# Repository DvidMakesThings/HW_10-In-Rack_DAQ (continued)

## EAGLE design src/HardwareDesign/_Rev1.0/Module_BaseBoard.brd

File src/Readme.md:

# %PROJECT_NAME% Project Design files
This repository contains source files for software and hardware designs related to the %PROJECT_NAME% project.
## Contents
- **Software**: Source code for the software components.
- **Hardware**: Design files for the hardware components.
## Usage
1. Clone the repository.
2. Navigate to the `src` directory.
3. Follow the instructions in the respective subdirectories for software and hardware.
## License
This project is licensed under the MIT License.
## Contact
For any questions or feedback, please contact:
- Email: [s.dvid@hotmail.com](mailto:s.dvid@hotmail.com)
- GitHub: [DvidMakesThings](https://github.com/DvidMakesThings)

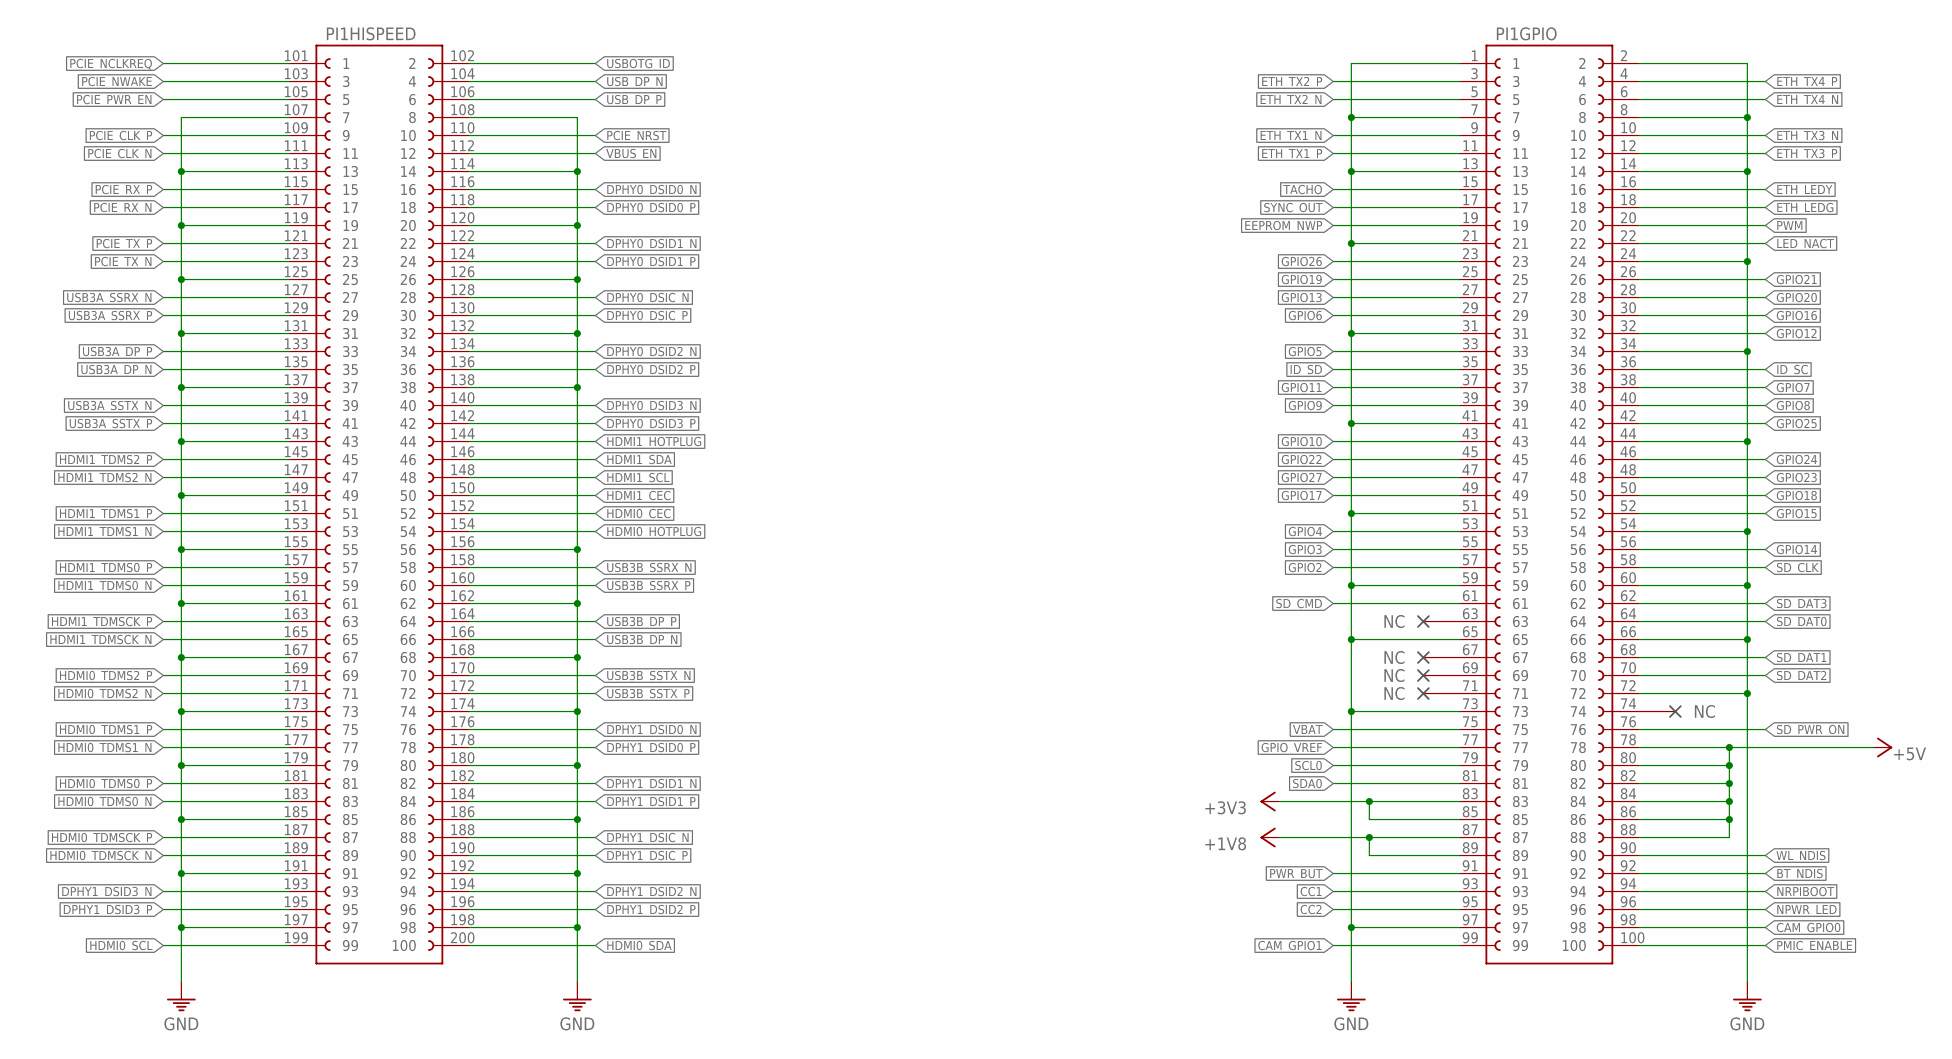
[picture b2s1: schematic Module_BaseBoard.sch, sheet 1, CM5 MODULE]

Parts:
PI1: RASPBERRY_CM5; CM5

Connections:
+1V8: PI1.87, PI1.89; also elsewhere on the board
+3V3: PI1.83, PI1.85; also elsewhere on the board
+5V: PI1.78, PI1.80, PI1.82, PI1.84, PI1.86, PI1.88; also elsewhere on the board
BT_NDIS: PI1.92; also elsewhere on the board
CAM_GPIO0: PI1.98; also elsewhere on the board
CAM_GPIO1: PI1.99; also elsewhere on the board
CC1: PI1.93; also elsewhere on the board
CC2: PI1.95; also elsewhere on the board
DPHY0_DSIC_N: PI1.128 (28); also elsewhere on the board
DPHY0_DSIC_P: PI1.130 (30); also elsewhere on the board
DPHY0_DSID0_N: PI1.116 (16); also elsewhere on the board
DPHY0_DSID0_P: PI1.118 (18); also elsewhere on the board
DPHY0_DSID1_N: PI1.122 (22); also elsewhere on the board
DPHY0_DSID1_P: PI1.124 (24); also elsewhere on the board
DPHY0_DSID2_N: PI1.134 (34); also elsewhere on the board
DPHY0_DSID2_P: PI1.136 (36); also elsewhere on the board
DPHY0_DSID3_N: PI1.140 (40); also elsewhere on the board
DPHY0_DSID3_P: PI1.142 (42); also elsewhere on the board
DPHY1_DSIC_N: PI1.188 (88); also elsewhere on the board
DPHY1_DSIC_P: PI1.190 (90); also elsewhere on the board
DPHY1_DSID0_N: PI1.176 (76); also elsewhere on the board
DPHY1_DSID0_P: PI1.178 (78); also elsewhere on the board
DPHY1_DSID1_N: PI1.182 (82); also elsewhere on the board
DPHY1_DSID1_P: PI1.184 (84); also elsewhere on the board
DPHY1_DSID2_N: PI1.194 (94); also elsewhere on the board
DPHY1_DSID2_P: PI1.196 (96); also elsewhere on the board
DPHY1_DSID3_N: PI1.193 (93); also elsewhere on the board
DPHY1_DSID3_P: PI1.195 (95); also elsewhere on the board
EEPROM_NWP: PI1.19; also elsewhere on the board
ETH_LEDG: PI1.18; also elsewhere on the board
ETH_LEDY: PI1.16; also elsewhere on the board
ETH_TX1_N: PI1.9; also elsewhere on the board
ETH_TX1_P: PI1.11; also elsewhere on the board
ETH_TX2_N: PI1.5; also elsewhere on the board
ETH_TX2_P: PI1.3; also elsewhere on the board
ETH_TX3_N: PI1.10; also elsewhere on the board
ETH_TX3_P: PI1.12; also elsewhere on the board
ETH_TX4_N: PI1.6; also elsewhere on the board
ETH_TX4_P: PI1.4; also elsewhere on the board
GND: PI1.1, PI1.2, PI1.7, PI1.8, PI1.13, PI1.14, PI1.21, PI1.24, PI1.31, PI1.34, PI1.41, PI1.44, PI1.51, PI1.54, PI1.59, PI1.60, PI1.65, PI1.66, PI1.72, PI1.73, PI1.97, PI1.107 (7), PI1.108 (8), PI1.113 (13), PI1.114 (14), PI1.119 (19), PI1.120 (20), PI1.125 (25), PI1.126 (26), PI1.131 (31), PI1.132 (32), PI1.137 (37), PI1.138 (38), PI1.143 (43), PI1.149 (49), PI1.155 (55), PI1.156 (56), PI1.161 (61), PI1.162 (62), PI1.167 (67), PI1.168 (68), PI1.173 (73), PI1.174 (74), PI1.179 (79), PI1.180 (80), PI1.185 (85), PI1.186 (86), PI1.191 (91), PI1.192 (92), PI1.197 (97), PI1.198 (98); also elsewhere on the board
GPIO2: PI1.57; also elsewhere on the board
GPIO3: PI1.55; also elsewhere on the board
GPIO4: PI1.53; also elsewhere on the board
GPIO5: PI1.33; also elsewhere on the board
GPIO6: PI1.29; also elsewhere on the board
GPIO7: PI1.38; also elsewhere on the board
GPIO8: PI1.40; also elsewhere on the board
GPIO9: PI1.39; also elsewhere on the board
GPIO10: PI1.43; also elsewhere on the board
GPIO11: PI1.37; also elsewhere on the board
GPIO12: PI1.32; also elsewhere on the board
GPIO13: PI1.27; also elsewhere on the board
GPIO14: PI1.56; also elsewhere on the board
GPIO15: PI1.52; also elsewhere on the board
GPIO16: PI1.30; also elsewhere on the board
GPIO17: PI1.49; also elsewhere on the board
GPIO18: PI1.50; also elsewhere on the board
GPIO19: PI1.25; also elsewhere on the board
GPIO20: PI1.28; also elsewhere on the board
GPIO21: PI1.26; also elsewhere on the board
GPIO22: PI1.45; also elsewhere on the board
GPIO23: PI1.48; also elsewhere on the board
GPIO24: PI1.46; also elsewhere on the board
GPIO25: PI1.42; also elsewhere on the board
GPIO26: PI1.23; also elsewhere on the board
GPIO27: PI1.47; also elsewhere on the board
GPIO_VREF: PI1.77; also elsewhere on the board
HDMI0_CEC: PI1.152 (52); also elsewhere on the board
HDMI0_HOTPLUG: PI1.154 (54); also elsewhere on the board
HDMI0_SCL: PI1.199 (99); also elsewhere on the board
HDMI0_SDA: PI1.200 (100); also elsewhere on the board
HDMI0_TDMS0_N: PI1.183 (83); also elsewhere on the board
HDMI0_TDMS0_P: PI1.181 (81); also elsewhere on the board
HDMI0_TDMS1_N: PI1.177 (77); also elsewhere on the board
HDMI0_TDMS1_P: PI1.175 (75); also elsewhere on the board
HDMI0_TDMS2_N: PI1.171 (71); also elsewhere on the board
HDMI0_TDMS2_P: PI1.169 (69); also elsewhere on the board
HDMI0_TDMSCK_N: PI1.189 (89); also elsewhere on the board
HDMI0_TDMSCK_P: PI1.187 (87); also elsewhere on the board
HDMI1_CEC: PI1.150 (50); also elsewhere on the board
HDMI1_HOTPLUG: PI1.144 (44); also elsewhere on the board
HDMI1_SCL: PI1.148 (48); also elsewhere on the board
HDMI1_SDA: PI1.146 (46); also elsewhere on the board
HDMI1_TDMS0_N: PI1.159 (59); also elsewhere on the board
HDMI1_TDMS0_P: PI1.157 (57); also elsewhere on the board
HDMI1_TDMS1_N: PI1.153 (53); also elsewhere on the board
HDMI1_TDMS1_P: PI1.151 (51); also elsewhere on the board
HDMI1_TDMS2_N: PI1.147 (47); also elsewhere on the board
HDMI1_TDMS2_P: PI1.145 (45); also elsewhere on the board
HDMI1_TDMSCK_N: PI1.165 (65); also elsewhere on the board
HDMI1_TDMSCK_P: PI1.163 (63); also elsewhere on the board
ID_SC: PI1.36; also elsewhere on the board
ID_SD: PI1.35; also elsewhere on the board
LED_NACT: PI1.22
NPWR_LED: PI1.96; also elsewhere on the board
NRPIBOOT: PI1.94; also elsewhere on the board
PCIE_CLK_N: PI1.111 (11); also elsewhere on the board
PCIE_CLK_P: PI1.109 (9); also elsewhere on the board
PCIE_NCLKREQ: PI1.101 (1); also elsewhere on the board
PCIE_NRST: PI1.110 (10); also elsewhere on the board
PCIE_NWAKE: PI1.103 (3); also elsewhere on the board
PCIE_PWR_EN: PI1.105 (5); also elsewhere on the board
PCIE_RX_N: PI1.117 (17); also elsewhere on the board
PCIE_RX_P: PI1.115 (15); also elsewhere on the board
PCIE_TX_N: PI1.123 (23); also elsewhere on the board
PCIE_TX_P: PI1.121 (21); also elsewhere on the board
PMIC_ENABLE: PI1.100; also elsewhere on the board
PWM: PI1.20; also elsewhere on the board
PWR_BUT: PI1.91; also elsewhere on the board
SCL0: PI1.79; also elsewhere on the board
SDA0: PI1.81; also elsewhere on the board
SD_CLK: PI1.58; also elsewhere on the board
SD_CMD: PI1.61; also elsewhere on the board
SD_DAT0: PI1.64; also elsewhere on the board
SD_DAT1: PI1.68; also elsewhere on the board
SD_DAT2: PI1.70; also elsewhere on the board
SD_DAT3: PI1.62; also elsewhere on the board
SD_PWR_ON: PI1.76; also elsewhere on the board
SYNC_OUT: PI1.17; also elsewhere on the board
TACHO: PI1.15; also elsewhere on the board
USB3A_DP_N: PI1.135 (35); also elsewhere on the board
USB3A_DP_P: PI1.133 (33); also elsewhere on the board
USB3A_SSRX_N: PI1.127 (27); also elsewhere on the board
USB3A_SSRX_P: PI1.129 (29); also elsewhere on the board
USB3A_SSTX_N: PI1.139 (39); also elsewhere on the board
USB3A_SSTX_P: PI1.141 (41); also elsewhere on the board
USB3B_DP_N: PI1.166 (66); also elsewhere on the board
USB3B_DP_P: PI1.164 (64); also elsewhere on the board
USB3B_SSRX_N: PI1.158 (58); also elsewhere on the board
USB3B_SSRX_P: PI1.160 (60); also elsewhere on the board
USB3B_SSTX_N: PI1.170 (70); also elsewhere on the board
USB3B_SSTX_P: PI1.172 (72); also elsewhere on the board
USBOTG_ID: PI1.102 (2); also elsewhere on the board
USB_DP_N: PI1.104 (4); also elsewhere on the board
USB_DP_P: PI1.106 (6); also elsewhere on the board
VBAT: PI1.75
VBUS_EN: PI1.112 (12); also elsewhere on the board
WL_NDIS: PI1.90; also elsewhere on the board

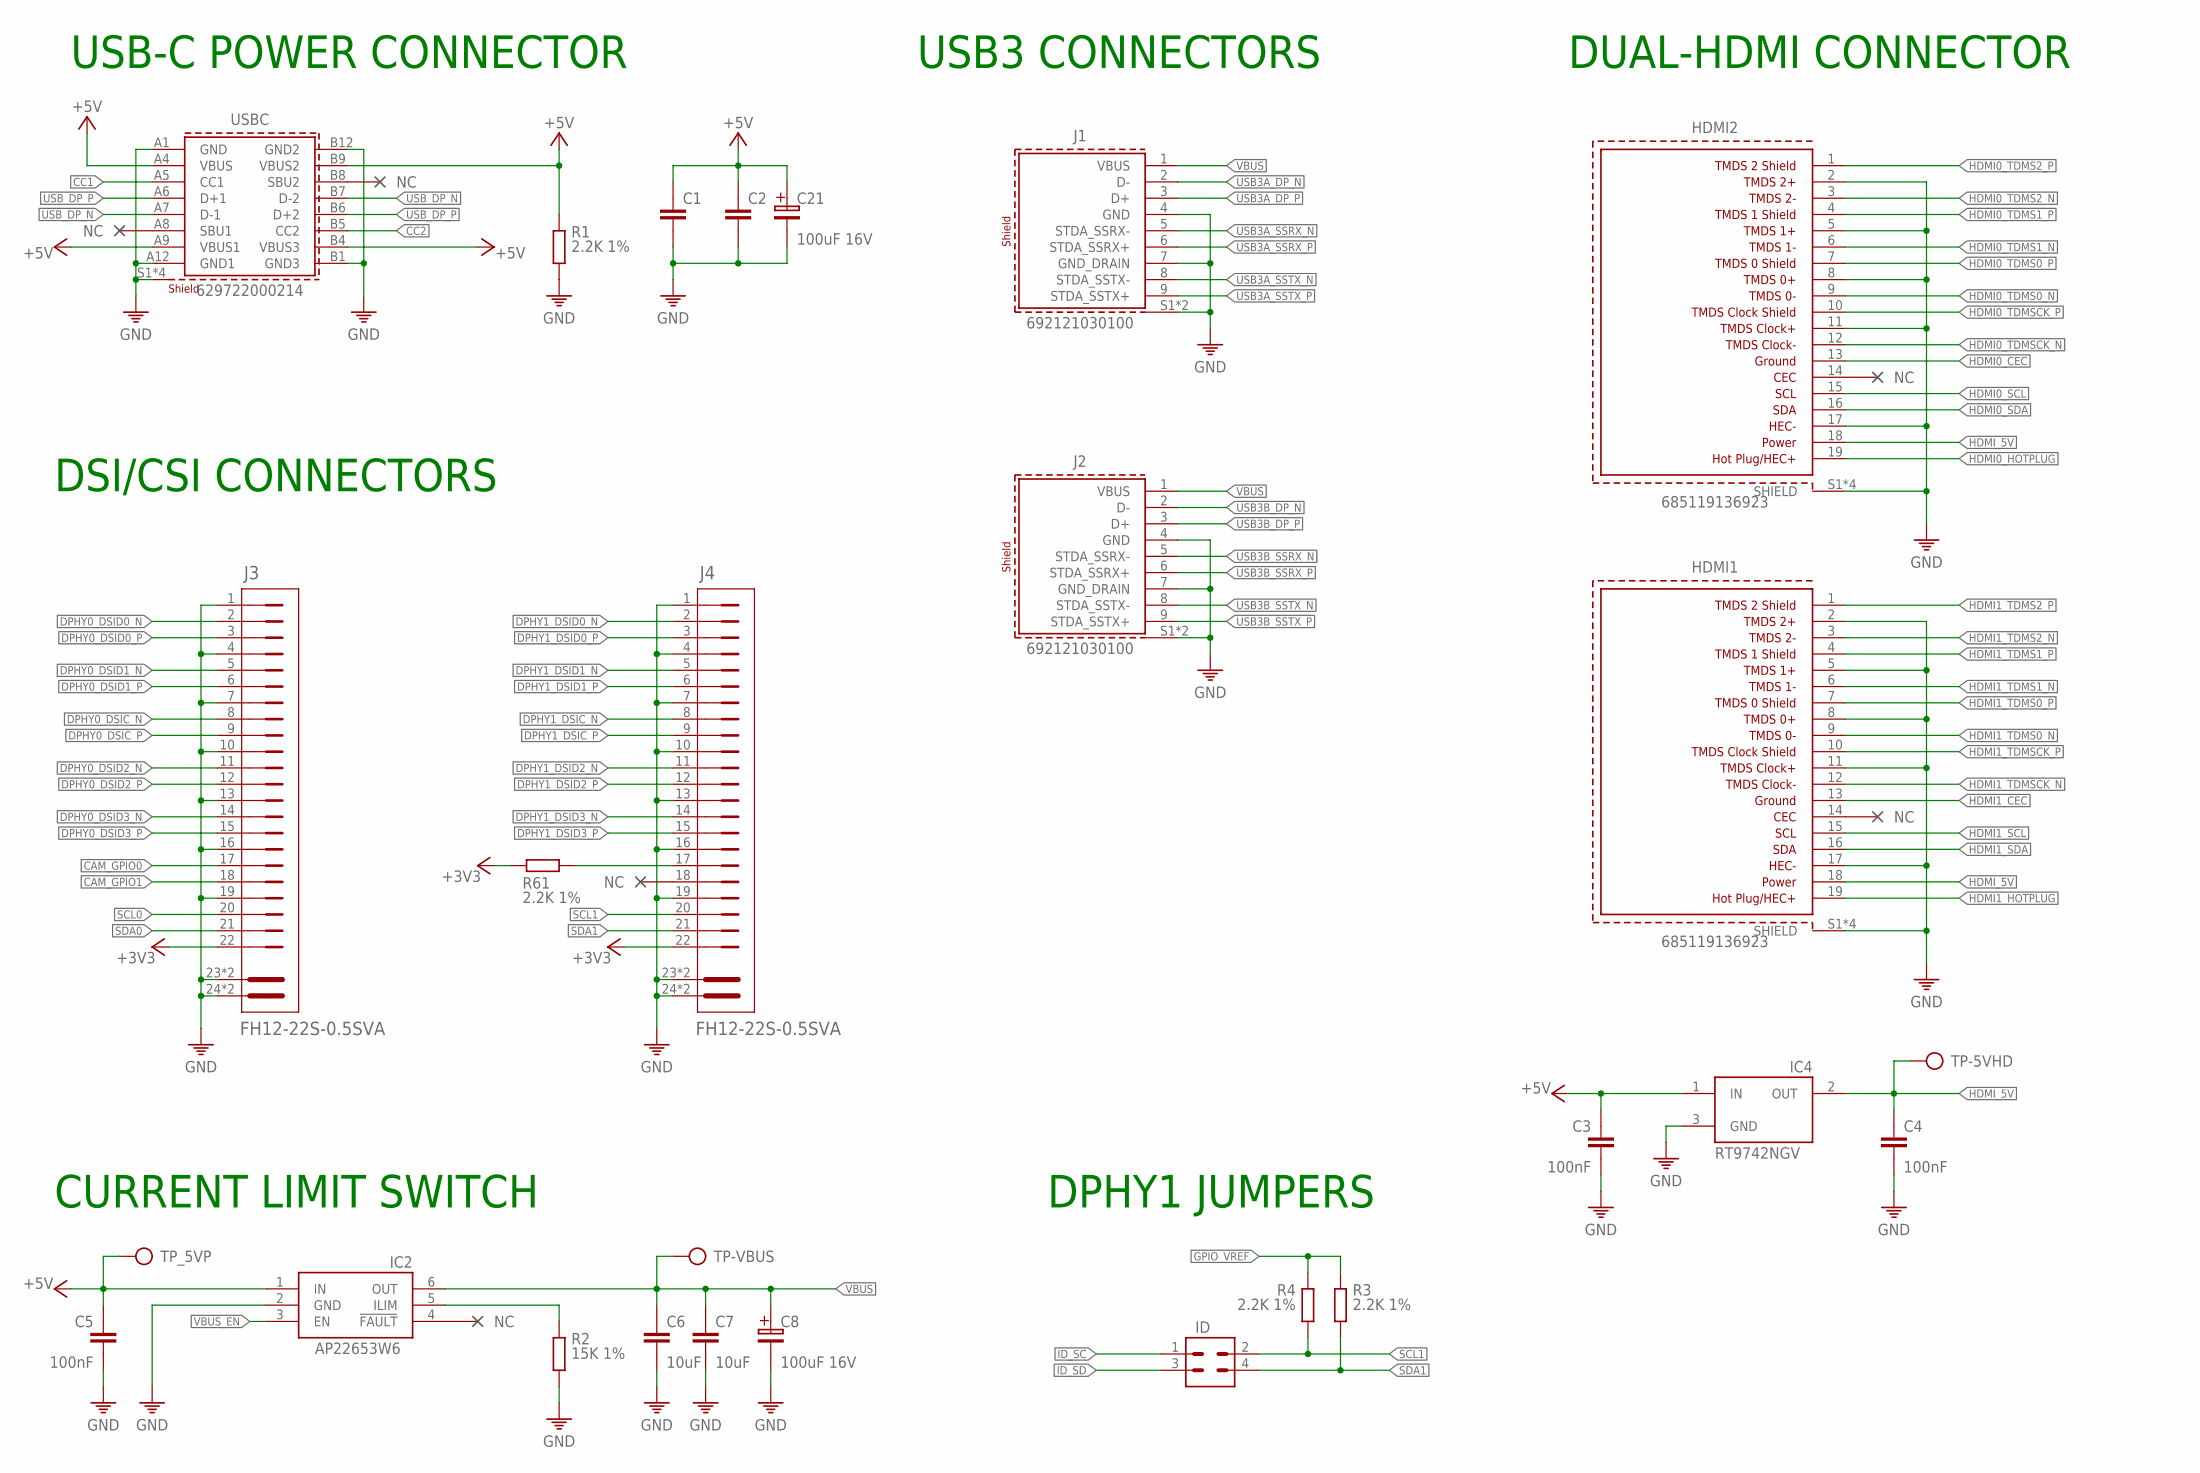
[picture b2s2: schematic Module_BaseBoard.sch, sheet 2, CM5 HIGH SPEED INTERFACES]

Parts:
C1, C2: C-0402; C0402
C3, C4, C5: 100nF; C0402
C6, C7: 10uF; C0805
C8, C21: 100uF 16V; 100UF-16V
HDMI1, HDMI2: 685119136923
IC2: AP22653W6; SOT23-6
IC4: RT9742NGV; SOT23
ID: CON-2X2; 2X2
J1, J2: 692121030100
J3, J4: FH12-22S-0.5SVA; FH12-22S-0.5SH
R1, R3, R4, R61: 2.2K 1%; 0402
R2: 15K 1%; 0402
TP-5VHD: TP
TP-VBUS: TP
TP_5VP: TP
USBC: 629722000214

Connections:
+3V3: J3.22, J4.22, R61.2; also elsewhere on the board
+5V: C1.1, C2.1, C3.1, C5.1, C21.1, IC2.1 (IN), IC4.1 (IN), R1.1, TP_5VP.TP, USBC.A4 (VBUS), USBC.A9 (VBUS1), USBC.B4 (VBUS3), USBC.B9 (VBUS2); also elsewhere on the board
CAM_GPIO0: J3.17; also elsewhere on the board
CAM_GPIO1: J3.18; also elsewhere on the board
CC1: USBC.A5 (CC1); also elsewhere on the board
CC2: USBC.B5 (CC2); also elsewhere on the board
DPHY0_DSIC_N: J3.8; also elsewhere on the board
DPHY0_DSIC_P: J3.9; also elsewhere on the board
DPHY0_DSID0_N: J3.2; also elsewhere on the board
DPHY0_DSID0_P: J3.3; also elsewhere on the board
DPHY0_DSID1_N: J3.5; also elsewhere on the board
DPHY0_DSID1_P: J3.6; also elsewhere on the board
DPHY0_DSID2_N: J3.11; also elsewhere on the board
DPHY0_DSID2_P: J3.12; also elsewhere on the board
DPHY0_DSID3_N: J3.14; also elsewhere on the board
DPHY0_DSID3_P: J3.15; also elsewhere on the board
DPHY1_DSIC_N: J4.8; also elsewhere on the board
DPHY1_DSIC_P: J4.9; also elsewhere on the board
DPHY1_DSID0_N: J4.2; also elsewhere on the board
DPHY1_DSID0_P: J4.3; also elsewhere on the board
DPHY1_DSID1_N: J4.5; also elsewhere on the board
DPHY1_DSID1_P: J4.6; also elsewhere on the board
DPHY1_DSID2_N: J4.11; also elsewhere on the board
DPHY1_DSID2_P: J4.12; also elsewhere on the board
DPHY1_DSID3_N: J4.14; also elsewhere on the board
DPHY1_DSID3_P: J4.15; also elsewhere on the board
GND: C1.2, C2.2, C3.2, C4.2, C5.2, C6.2, C7.2, C8.2, C21.2, HDMI1.2 (TMDS2+), HDMI1.5 (TMDSDATA1+), HDMI1.8 (TMDS0+), HDMI1.11 (TMDSCLOCK+), HDMI1.17 (UTILITY/HEAC+), HDMI1.S1 (SHIELD), HDMI1.S2 (SHIELD), HDMI1.S3 (SHIELD), HDMI1.S4 (SHIELD), HDMI2.2 (TMDS2+), HDMI2.5 (TMDSDATA1+), HDMI2.8 (TMDS0+), HDMI2.11 (TMDSCLOCK+), HDMI2.17 (UTILITY/HEAC+), HDMI2.S1 (SHIELD), HDMI2.S2 (SHIELD), HDMI2.S3 (SHIELD), HDMI2.S4 (SHIELD), IC2.2 (GND), IC4.3 (GND), J1.4 (GND), J1.7 (GND_DRAIN), J1.S1 (SHIELD), J1.S2 (SHIELD), J2.4 (GND), J2.7 (GND_DRAIN), J2.S1 (SHIELD), J2.S2 (SHIELD), J3.1, J3.4, J3.7, J3.10, J3.13, J3.16, J3.19, J3.23 (MH1), J3.24 (MH2), J3.25 (MH1), J3.26 (MH2), J4.1, J4.4, J4.7, J4.10, J4.13, J4.16, J4.19, J4.23 (MH1), J4.24 (MH2), J4.25 (MH1), J4.26 (MH2), R1.2, R2.2, USBC.A1 (GND), USBC.A12 (GND1), USBC.B1 (GND3), USBC.B12 (GND2), USBC.S1 (SHIELD), USBC.S2 (SHIELD), USBC.S3 (SHIELD), USBC.S4 (SHIELD); also elsewhere on the board
GPIO_VREF: R3.1, R4.1; also elsewhere on the board
HDMI0_CEC: HDMI2.13 (GROUND); also elsewhere on the board
HDMI0_HOTPLUG: HDMI2.19 (HOTPLUG/HEC+); also elsewhere on the board
HDMI0_SCL: HDMI2.15 (SCL); also elsewhere on the board
HDMI0_SDA: HDMI2.16 (SDA); also elsewhere on the board
HDMI0_TDMS0_N: HDMI2.9 (TMDS0-); also elsewhere on the board
HDMI0_TDMS0_P: HDMI2.7 (TMDS0SHIELD); also elsewhere on the board
HDMI0_TDMS1_N: HDMI2.6 (TMDS1-); also elsewhere on the board
HDMI0_TDMS1_P: HDMI2.4 (TMDS1SHIELD); also elsewhere on the board
HDMI0_TDMS2_N: HDMI2.3 (TMDS2-); also elsewhere on the board
HDMI0_TDMS2_P: HDMI2.1 (TMDS2SHIELD); also elsewhere on the board
HDMI0_TDMSCK_N: HDMI2.12 (TMDSCLOCK-); also elsewhere on the board
HDMI0_TDMSCK_P: HDMI2.10 (TMDSCLOCKSHIELD); also elsewhere on the board
HDMI1_CEC: HDMI1.13 (GROUND); also elsewhere on the board
HDMI1_HOTPLUG: HDMI1.19 (HOTPLUG/HEC+); also elsewhere on the board
HDMI1_SCL: HDMI1.15 (SCL); also elsewhere on the board
HDMI1_SDA: HDMI1.16 (SDA); also elsewhere on the board
HDMI1_TDMS0_N: HDMI1.9 (TMDS0-); also elsewhere on the board
HDMI1_TDMS0_P: HDMI1.7 (TMDS0SHIELD); also elsewhere on the board
HDMI1_TDMS1_N: HDMI1.6 (TMDS1-); also elsewhere on the board
HDMI1_TDMS1_P: HDMI1.4 (TMDS1SHIELD); also elsewhere on the board
HDMI1_TDMS2_N: HDMI1.3 (TMDS2-); also elsewhere on the board
HDMI1_TDMS2_P: HDMI1.1 (TMDS2SHIELD); also elsewhere on the board
HDMI1_TDMSCK_N: HDMI1.12 (TMDSCLOCK-); also elsewhere on the board
HDMI1_TDMSCK_P: HDMI1.10 (TMDSCLOCKSHIELD); also elsewhere on the board
HDMI_5V: C4.1, HDMI1.18 (POWER), HDMI2.18 (POWER), IC4.2 (OUT), TP-5VHD.TP
ID_SC: ID.1; also elsewhere on the board
ID_SD: ID.3; also elsewhere on the board
unnamed: IC2.5 (ILIM), R2.1
unnamed: J4.17, R61.1
SCL0: J3.20; also elsewhere on the board
SCL1: ID.2, J4.20, R4.2
SDA0: J3.21; also elsewhere on the board
SDA1: ID.4, J4.21, R3.2
USB3A_DP_N: J1.2 (D-); also elsewhere on the board
USB3A_DP_P: J1.3 (D+); also elsewhere on the board
USB3A_SSRX_N: J1.5 (STDA_SSRX-); also elsewhere on the board
USB3A_SSRX_P: J1.6 (STDA_SSRX+); also elsewhere on the board
USB3A_SSTX_N: J1.8 (STDA_SSTX-); also elsewhere on the board
USB3A_SSTX_P: J1.9 (STDA_SSTX+); also elsewhere on the board
USB3B_DP_N: J2.2 (D-); also elsewhere on the board
USB3B_DP_P: J2.3 (D+); also elsewhere on the board
USB3B_SSRX_N: J2.5 (STDA_SSRX-); also elsewhere on the board
USB3B_SSRX_P: J2.6 (STDA_SSRX+); also elsewhere on the board
USB3B_SSTX_N: J2.8 (STDA_SSTX-); also elsewhere on the board
USB3B_SSTX_P: J2.9 (STDA_SSTX+); also elsewhere on the board
USB_DP_N: USBC.A7 (D-1), USBC.B7 (D-2); also elsewhere on the board
USB_DP_P: USBC.A6 (D+1), USBC.B6 (D+2); also elsewhere on the board
VBUS: C6.1, C7.1, C8.1, IC2.6 (OUT), J1.1 (VBUS), J2.1 (VBUS), TP-VBUS.TP
VBUS_EN: IC2.3 (EN); also elsewhere on the board

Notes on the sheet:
USB-C POWER CONNECTOR
USB3 CONNECTORS
DUAL-HDMI CONNECTOR
CURRENT LIMIT SWITCH
DPHY1 JUMPERS
DSI/CSI CONNECTORS

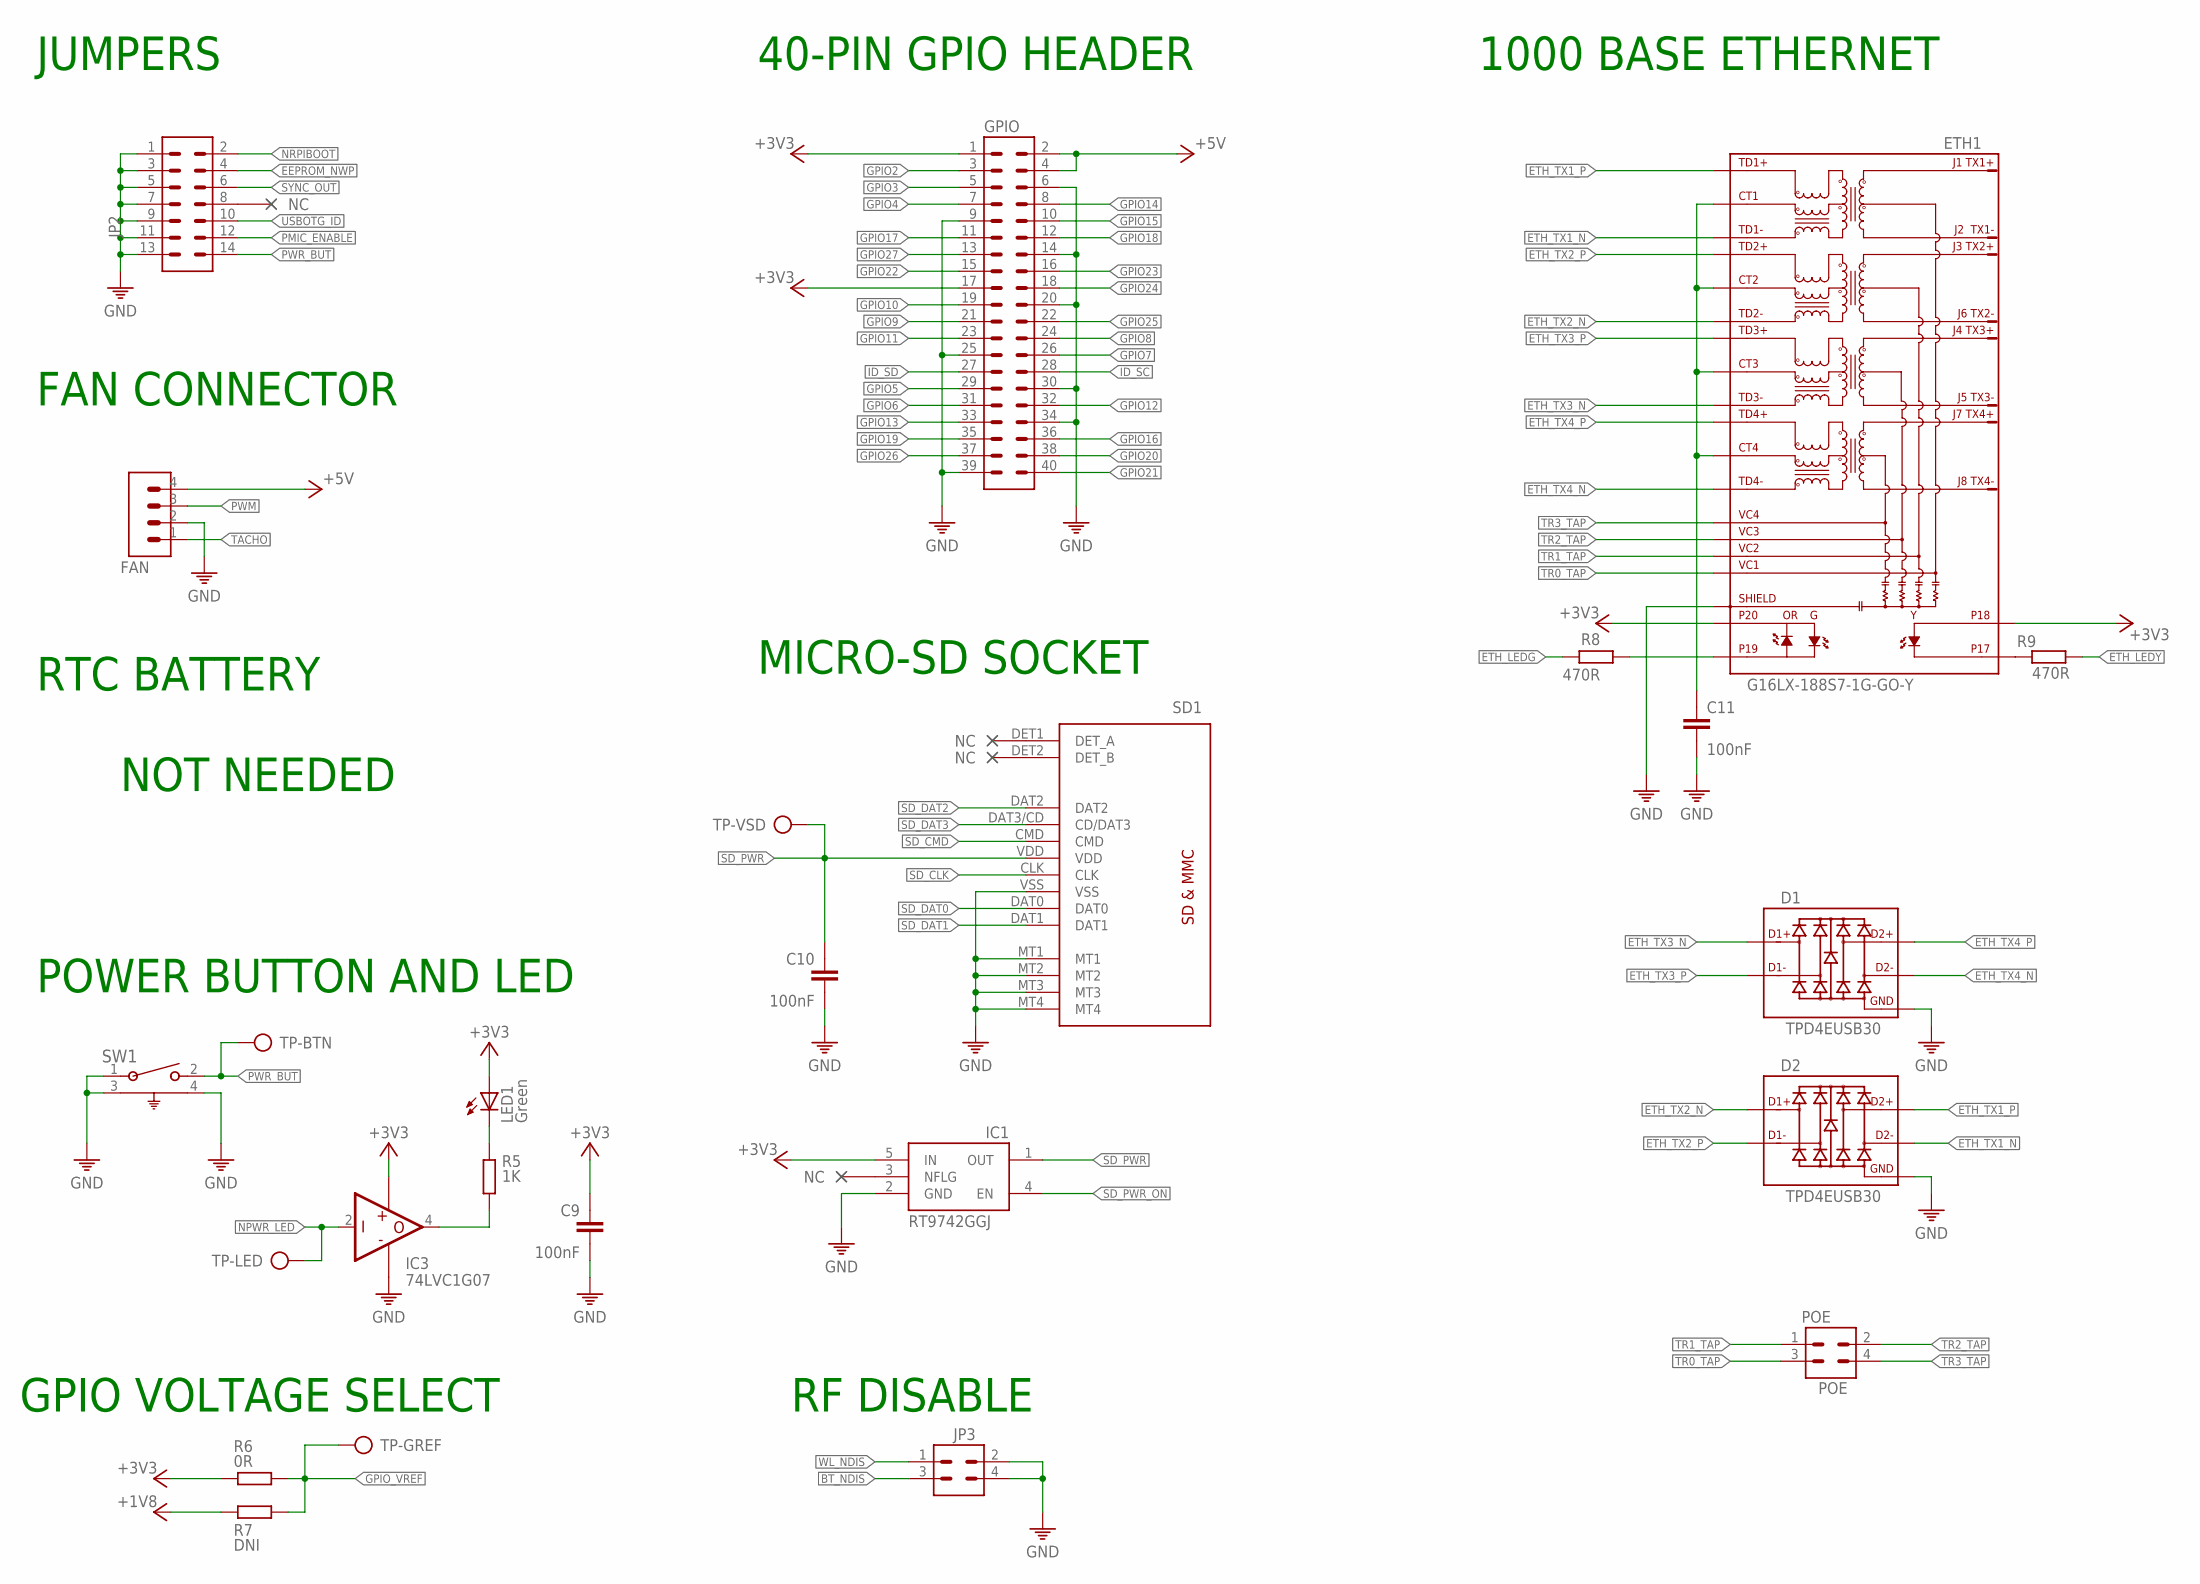
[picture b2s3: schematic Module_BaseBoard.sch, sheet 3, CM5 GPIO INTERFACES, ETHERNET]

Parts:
C9, C10, C11: 100nF; C0402
D1, D2: TPD4EUSB30; USON
ETH1: G16LX-188S7-1G-GO-Y; MAGJACK_POE
FAN: CON-1X4; 1X4
GPIO: CON-2X20; 2X20
IC1: RT9742GGJ; SOT23-5
IC3: 74LVC1G07; SOT23-5
JP2: CON-2X7; 2X7
JP3: CON-2X2; 2X2
LED1: Green; CHIPLED_0805
POE: POE; 2X2
R5: 1K; 0402
R6: 0R; 0402
R7: DNI; 0402
R8, R9: 470R; 0402
SD1: MICRO-SD; MICROSD
SW1: 1825027-8; SW2_1825027-C_TEC
TP-BTN: TP
TP-GREF: TP
TP-LED: TP
TP-VSD: TP

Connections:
+1V8: R7.1; also elsewhere on the board
+3V3: C9.1, ETH1.18, ETH1.20, GPIO.1, GPIO.17, IC1.5 (IN), IC3.5 (VCC), LED1.A, R6.1; also elsewhere on the board
+5V: FAN.4, GPIO.2, GPIO.4; also elsewhere on the board
BT_NDIS: JP3.3; also elsewhere on the board
EEPROM_NWP: JP2.4; also elsewhere on the board
ETH_LEDG: R8.1; also elsewhere on the board
ETH_LEDY: R9.2; also elsewhere on the board
ETH_TX1_N: D2.2 (D1-), D2.9 (D1-), ETH1.TD1-; also elsewhere on the board
ETH_TX1_P: D2.1 (D1+), D2.10 (D1+), ETH1.TD1+; also elsewhere on the board
ETH_TX2_N: D2.4 (D2+), D2.7 (D2+), ETH1.TD2-; also elsewhere on the board
ETH_TX2_P: D2.5 (D2-), D2.6 (D2-), ETH1.TD2+; also elsewhere on the board
ETH_TX3_N: D1.4 (D2+), D1.7 (D2+), ETH1.TD3-; also elsewhere on the board
ETH_TX3_P: D1.5 (D2-), D1.6 (D2-), ETH1.TD3+; also elsewhere on the board
ETH_TX4_N: D1.2 (D1-), D1.9 (D1-), ETH1.TD4-; also elsewhere on the board
ETH_TX4_P: D1.1 (D1+), D1.10 (D1+), ETH1.TD4+; also elsewhere on the board
GND: C9.2, C10.2, C11.2, D1.3 (GND), D1.8 (GND), D2.3 (GND), D2.8 (GND), ETH1.MH3 (SHIELD), ETH1.MH4 (SHIELD), FAN.2, GPIO.6, GPIO.9, GPIO.14, GPIO.20, GPIO.25, GPIO.30, GPIO.34, GPIO.39, IC1.2 (GND), IC3.3 (GND), JP2.1, JP2.3, JP2.5, JP2.7, JP2.9, JP2.11, JP2.13, JP3.2, JP3.4, SD1.MT1, SD1.MT2, SD1.MT3, SD1.MT4, SD1.VSS, SW1.1, SW1.3, SW1.4; also elsewhere on the board
GPIO2: GPIO.3; also elsewhere on the board
GPIO3: GPIO.5; also elsewhere on the board
GPIO4: GPIO.7; also elsewhere on the board
GPIO5: GPIO.29; also elsewhere on the board
GPIO6: GPIO.31; also elsewhere on the board
GPIO7: GPIO.26; also elsewhere on the board
GPIO8: GPIO.24; also elsewhere on the board
GPIO9: GPIO.21; also elsewhere on the board
GPIO10: GPIO.19; also elsewhere on the board
GPIO11: GPIO.23; also elsewhere on the board
GPIO12: GPIO.32; also elsewhere on the board
GPIO13: GPIO.33; also elsewhere on the board
GPIO14: GPIO.8; also elsewhere on the board
GPIO15: GPIO.10; also elsewhere on the board
GPIO16: GPIO.36; also elsewhere on the board
GPIO17: GPIO.11; also elsewhere on the board
GPIO18: GPIO.12; also elsewhere on the board
GPIO19: GPIO.35; also elsewhere on the board
GPIO20: GPIO.38; also elsewhere on the board
GPIO21: GPIO.40; also elsewhere on the board
GPIO22: GPIO.15; also elsewhere on the board
GPIO23: GPIO.16; also elsewhere on the board
GPIO24: GPIO.18; also elsewhere on the board
GPIO25: GPIO.22; also elsewhere on the board
GPIO26: GPIO.37; also elsewhere on the board
GPIO27: GPIO.13; also elsewhere on the board
GPIO_VREF: R6.2, R7.2, TP-GREF.TP; also elsewhere on the board
ID_SC: GPIO.28; also elsewhere on the board
ID_SD: GPIO.27; also elsewhere on the board
unnamed: LED1.C, R5.1
unnamed: IC3.4 (Y), R5.2
unnamed: C11.1, ETH1.CT1, ETH1.CT2, ETH1.CT3, ETH1.CT4
unnamed: ETH1.17, R9.1
unnamed: ETH1.19, R8.2
NPWR_LED: IC3.2 (A), TP-LED.TP; also elsewhere on the board
NRPIBOOT: JP2.2; also elsewhere on the board
PMIC_ENABLE: JP2.12; also elsewhere on the board
PWM: FAN.3; also elsewhere on the board
PWR_BUT: JP2.14, SW1.2, TP-BTN.TP; also elsewhere on the board
SD_CLK: SD1.CLK; also elsewhere on the board
SD_CMD: SD1.CMD; also elsewhere on the board
SD_DAT0: SD1.DAT0; also elsewhere on the board
SD_DAT1: SD1.DAT1; also elsewhere on the board
SD_DAT2: SD1.DAT2; also elsewhere on the board
SD_DAT3: SD1.DAT3/CD (CD/DAT3); also elsewhere on the board
SD_PWR: C10.1, IC1.1 (OUT), SD1.VDD, TP-VSD.TP
SD_PWR_ON: IC1.4 (EN); also elsewhere on the board
SYNC_OUT: JP2.6; also elsewhere on the board
TACHO: FAN.1; also elsewhere on the board
TR0_TAP: ETH1.VC1, POE.3
TR1_TAP: ETH1.VC2, POE.1
TR2_TAP: ETH1.VC3, POE.2
TR3_TAP: ETH1.VC4, POE.4
USBOTG_ID: JP2.10; also elsewhere on the board
WL_NDIS: JP3.1; also elsewhere on the board

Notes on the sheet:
JUMPERS
FAN CONNECTOR
RTC BATTERY
POWER BUTTON AND LED
GPIO VOLTAGE SELECT
40-PIN GPIO HEADER
MICRO-SD SOCKET
1000 BASE ETHERNET
RF DISABLE
NOT NEEDED
